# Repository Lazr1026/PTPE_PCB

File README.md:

# PTPE_PCB
PCB for the Pico ToyPad Emulator

## BOM
- Pico (duh).
- [This screen](https://www.amazon.com/Display-Module-ST7735-128x160-STM32/dp/B07BFV69DZ). You can probably find something similar somewhere else for cheaper, but thats what I bought.
- [These tactile switches](https://www.amazon.com/1825910-6-Switch-Tactile-SPST-NO-0-05A/dp/B0CGYQHS7K) (the buttons). You can find cheaper probably on AliExpress, just search for "1825910-6". Make sure you get 5!

## Ordering Instructions
- Download and upload the `.zip` from the releases to JLCPCB / PCBWAY / OSHPark / etc.
- PCB does not need any specific option set, recommended to leave at defaults. You can do ENIG if you want, but that will jump the price way up.

## Assembly instructions
NOTE: Buttons and Screen can be done in any order you want, however the Pico MUST be done first.
- Start with soldering on the Pico. The screen will get in the way and the buttons *might*.
- Solder the buttons. (Or you can skip this and just use tweezers)
- Solder wires to the SD card pads (I recommend magnet wire for this), and then solder on the screen.
- Solder the SD card wires to the SD card pins on the screen.

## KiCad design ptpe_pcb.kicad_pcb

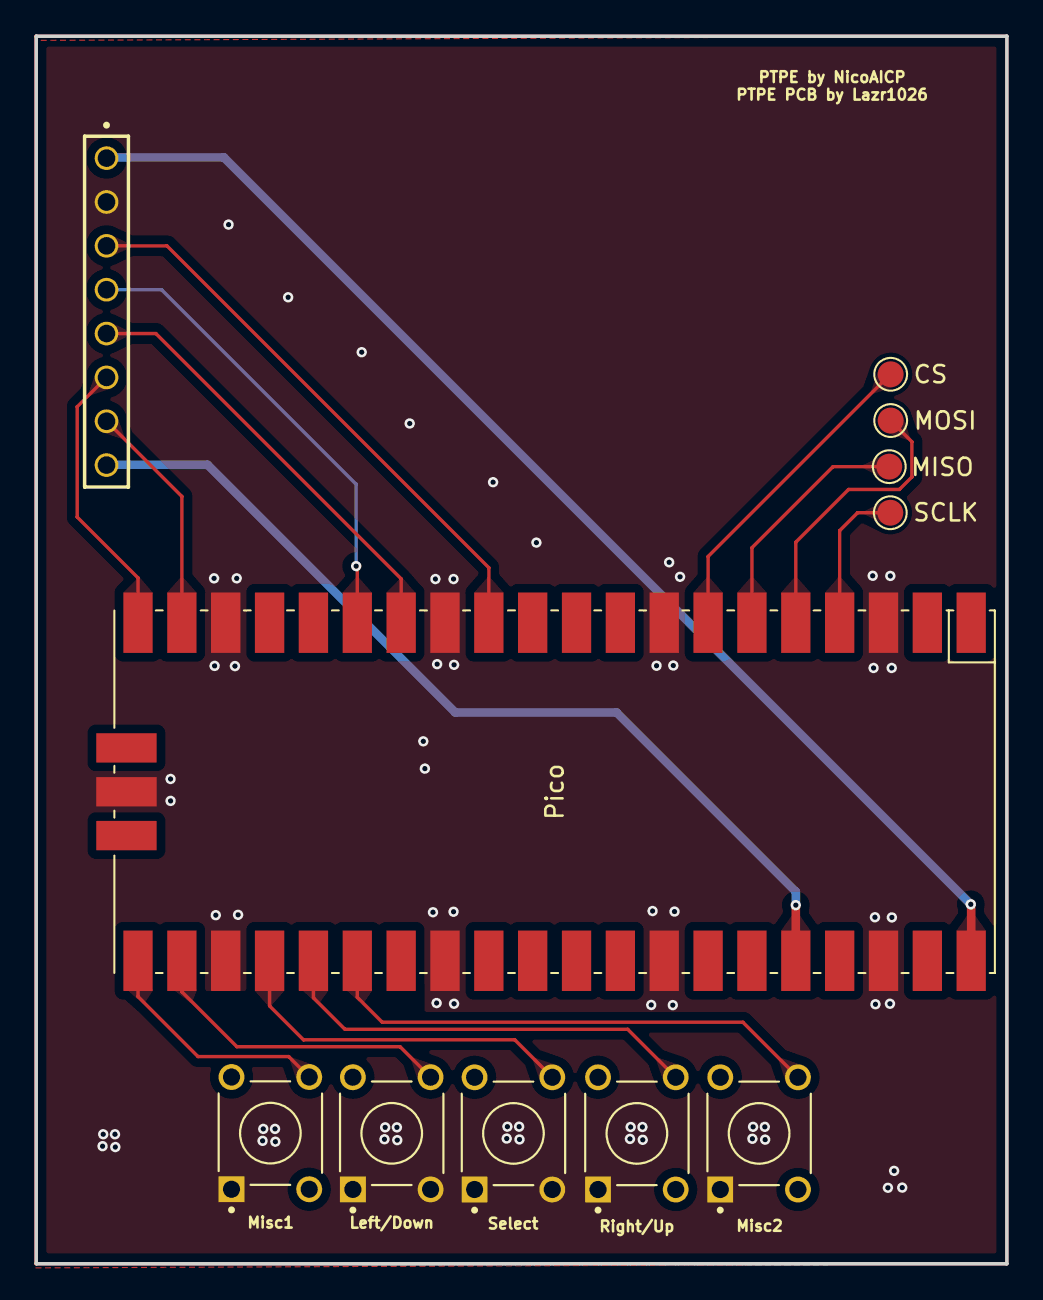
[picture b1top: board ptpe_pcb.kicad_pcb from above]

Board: 2 copper layers, 56.2 x 71.1 mm, 7 parts (0 on the bottom side), 7 nets.

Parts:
CS: TestPoint_Pad_D1.5mm
Left/Down: 1825910-6; SW_1825910-6-4
Misc1, Misc2: 1825910-6; SW_1825910-6-4
Pico: U1; RPi_Pico_SMD
Right/Up: 1825910-6; SW_1825910-6-4
Select: 1825910-6; SW_1825910-6-4

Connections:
CS: CS.1, Pico.7 (GPIO5), Pico.12 (GPIO9)
GND: Left/Down.1, Left/Down.3, Misc1.1, Misc2.1, Pico.3 (GND), Pico.8 (GND), Pico.13 (GND), Pico.18 (GND), Pico.23 (GND), Pico.28 (GND), Pico.33 (AGND), Pico.38 (GND), Pico.42 (GND), Right/Up.1, Select.1, Select.3
unnamed: Misc1.4, Pico.21 (GPIO16)
unnamed: Left/Down.4, Pico.22 (GPIO17)
unnamed: Pico.24 (GPIO18), Select.4
unnamed: Pico.25 (GPIO19), Right/Up.4
unnamed: Misc2.4, Pico.26 (GPIO20)

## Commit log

2024-08-30 Add pictures
2024-09-11 Add instructions.
2024-09-19 Fix a *lot* of mistakes present in Rev1
2024-09-19 Remove outdated gerber zip
2024-09-19 Somehow I forgot to upload the latest KiCAD files..
2024-09-19 Rev 2
